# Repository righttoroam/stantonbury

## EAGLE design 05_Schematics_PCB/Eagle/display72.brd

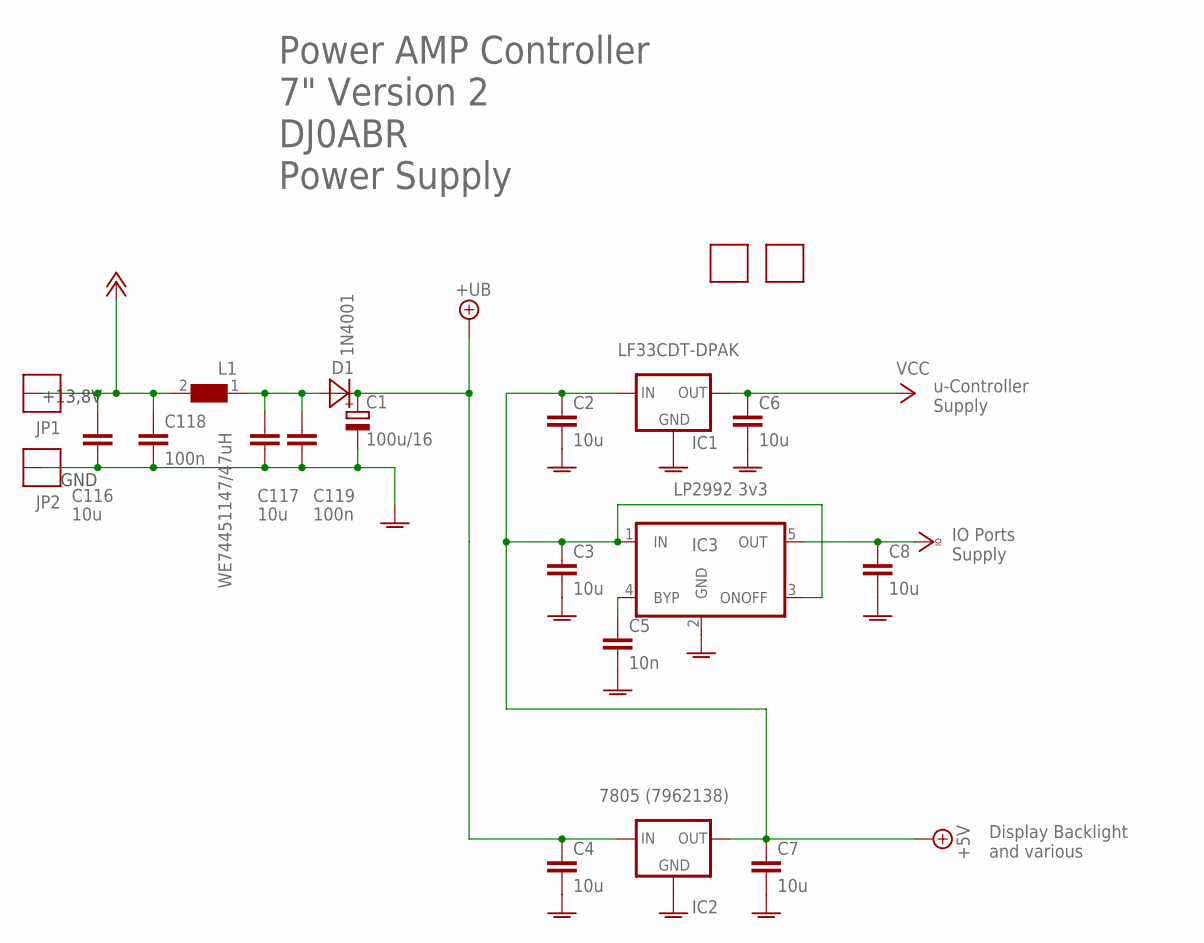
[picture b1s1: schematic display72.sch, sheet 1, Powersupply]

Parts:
C1: 100u/16; E2,5-7
C2, C3, C4, C116, C117: 10u; C0805
C5: 10n; C0603
C6, C7, C8: 10u; C0603
C118, C119: 100n; C0603
D1: 1N4001; MELF
FID1, FID2: FIDUCIAL
IC1: LF33CDT-DPAK; DPACK
IC2: 7805 (7962138); 78SR_SWITCHREG
IC3: LP2992 3v3; SOT23-5
JP1, JP2: THICKPINSQUARE; THICKPIN
L1: WE74451147/47uH; S

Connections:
+5V: C2.1, C3.1, C7.1, IC1.1 (IN), IC2.3 (OUT), IC3.1 (IN), IC3.3 (ONOFF); also elsewhere on the board
+UB: C1.+, C4.1, D1.1 (C), IC2.1 (IN)
AGND: C1.-, C2.2, C3.2, C4.2, C5.2, C6.2, C7.2, C8.2, C116.2, C117.2, C118.2, C119.2, IC1.4 (GND), IC2.2 (GND), IC3.2 (GND), JP2.1; also elsewhere on the board
unnamed: C117.1, C119.1, D1.2 (A), L1.1
unnamed: C5.1, IC3.4 (BYP)
PLUSZWOELF: C116.1, C118.1, JP1.1, L1.2; also elsewhere on the board
VCC: C6.1, IC1.3 (OUT); also elsewhere on the board
VCCIO: C8.1, IC3.5 (OUT); also elsewhere on the board

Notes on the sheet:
GND
+13,8V
Power AMP Controller 7" Version 2 DJ0ABR Power Supply
u-Controller Supply
IO Ports Supply
Display Backlight and various

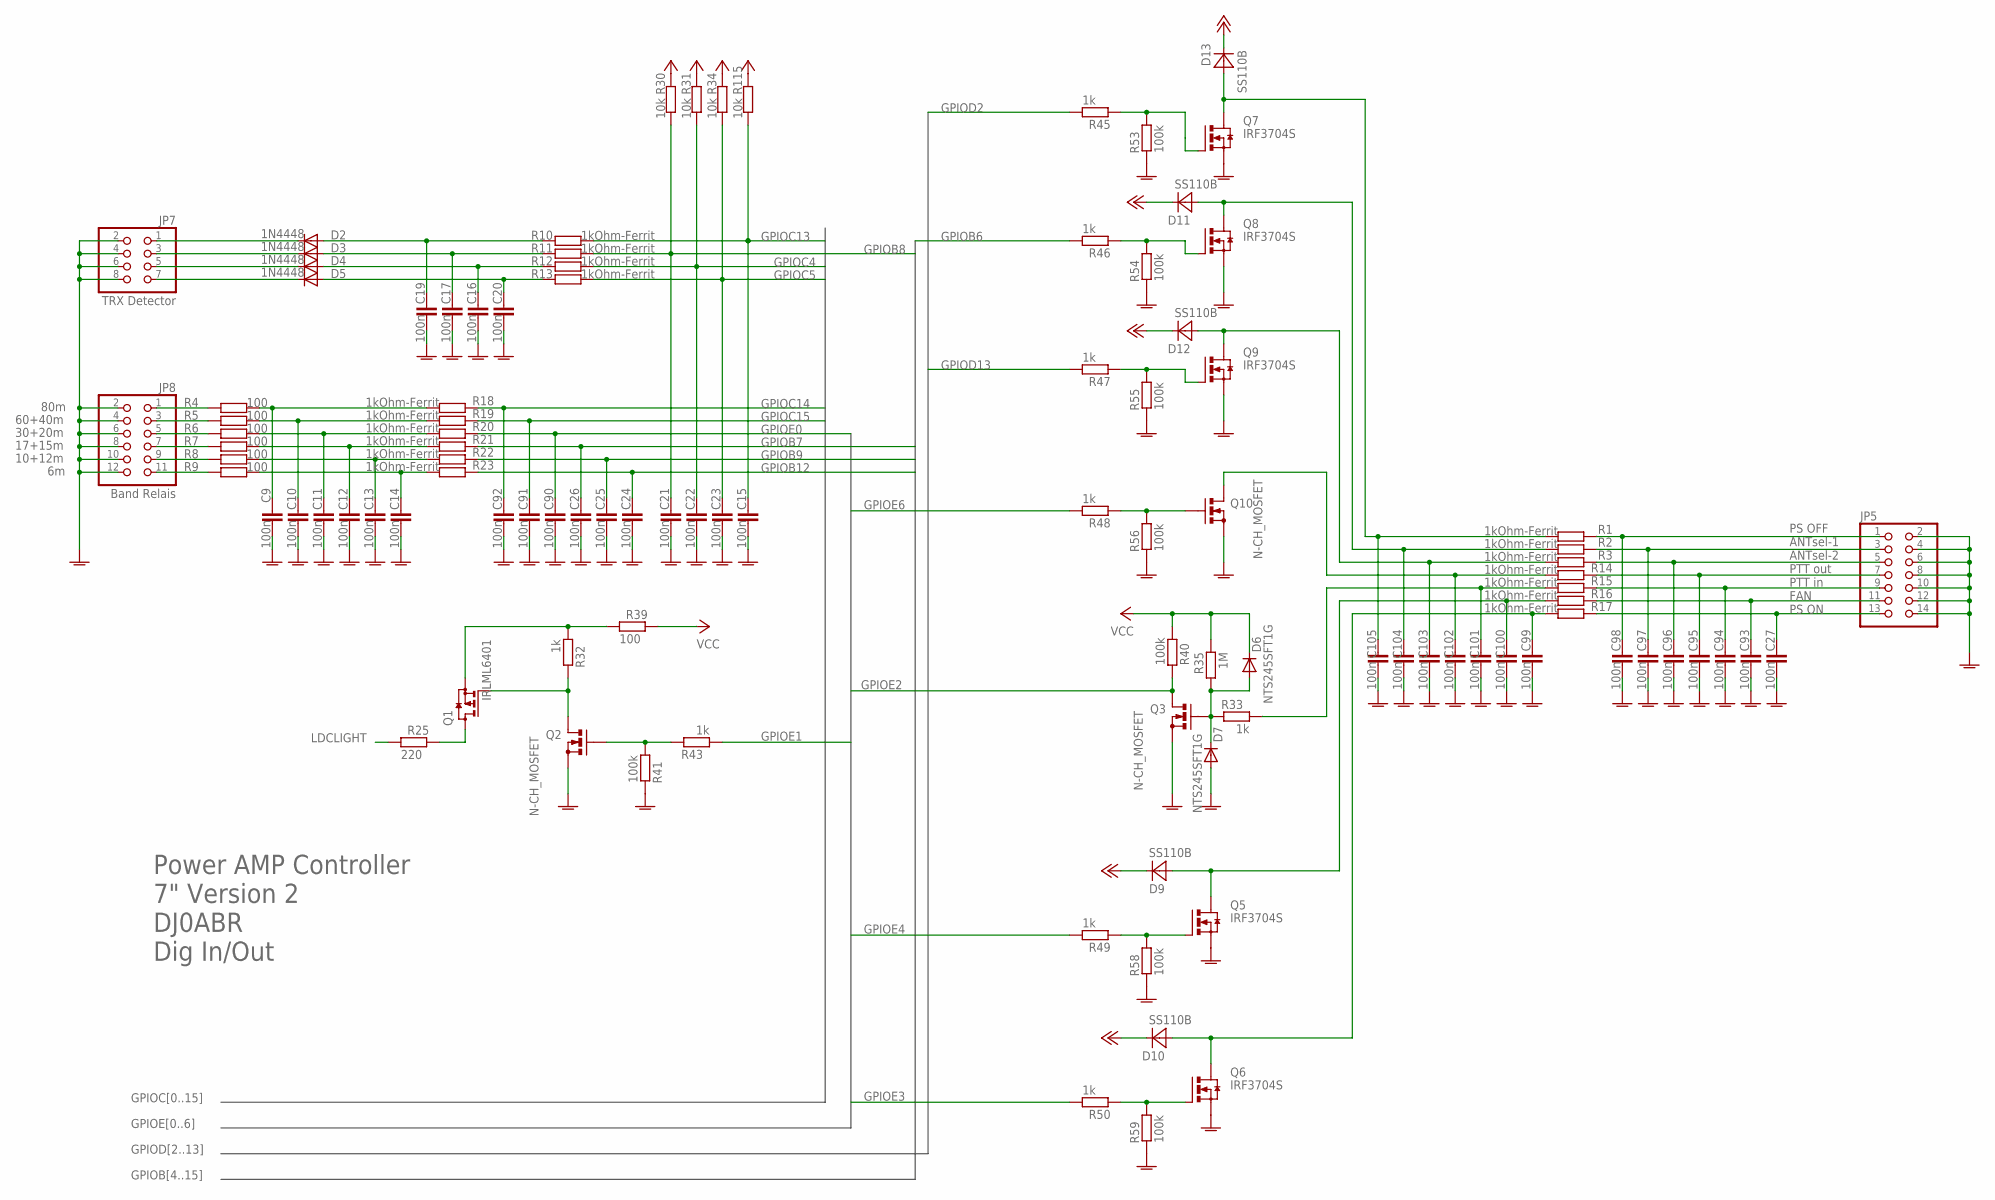
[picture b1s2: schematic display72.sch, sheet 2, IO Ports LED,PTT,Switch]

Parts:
C9, C10, C11, C12, C13, C14, C15, C16, C17, C19, C20, C21, C22, C23, C24, C25, C26, C27, C90, C91, C92, C93, C94, C95, C96, C97, C98, C99, C100, C101, C102, C103, C104, C105: 100n; C0603
D2, D3, D4, D5: 1N4448; SOD523
D6, D7: NTS245SFT1G; MINIMELF
D9, D10, D11, D12, D13: SS110B; MELF
JP5: PINHD-2X7/90; 2X07/90
JP7: TRX Detector; 2X04/90
JP8: Band Relais; 2X06/90
Q1: IRLML6401; SOT23
Q2, Q3, Q10: N-CH_MOSFET; SOT23
Q5, Q6, Q7, Q8, Q9: IRF3704S; D2PACK
R1, R2, R3, R10, R11, R12, R13, R14, R15, R16, R17, R18, R19, R20, R21, R22, R23: 1kOhm-Ferrit; R0603
R4, R5, R6, R7, R8, R9, R39: 100; R0603
R25: 220; R0603
R30, R31, R34, R115: 10k; R0603
R32, R33, R43, R45, R46, R47, R48, R49, R50: 1k; R0603
R35: 1M; R0603
R40, R41, R53, R54, R55, R56, R58, R59: 100k; R0603

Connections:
AGND: C9.2, C10.2, C11.2, C12.2, C13.2, C14.2, C15.2, C16.2, C17.2, C19.2, C20.2, C21.2, C22.2, C23.2, C24.2, C25.2, C26.2, C27.2, C90.2, C91.2, C92.2, C93.2, C94.2, C95.2, C96.2, C97.2, C98.2, C99.2, C100.2, C101.2, C102.2, C103.2, C104.2, C105.2, D7.A, JP5.2, JP5.4, JP5.6, JP5.8, JP5.10, JP5.12, JP5.14, JP7.2, JP7.4, JP7.6, JP7.8, JP8.2, JP8.4, JP8.6, JP8.8, JP8.10, JP8.12, Q2.2 (S), Q3.2 (S), Q5.3 (S), Q6.3 (S), Q7.3 (S), Q8.3 (S), Q9.3 (S), Q10.2 (S), R41.2, R53.2, R54.2, R55.2, R56.2, R58.2, R59.2; also elsewhere on the board
GPIOB6: R46.1; also elsewhere on the board
GPIOB7: C26.1, R21.1; also elsewhere on the board
GPIOB8: C21.1, R11.2, R30.1; also elsewhere on the board
GPIOB9: C25.1, R22.1; also elsewhere on the board
GPIOB12: C24.1, R23.1; also elsewhere on the board
GPIOC4: C22.1, R12.2, R31.1; also elsewhere on the board
GPIOC5: C23.1, R13.2, R34.1; also elsewhere on the board
GPIOC13: C15.1, R10.2, R115.1; also elsewhere on the board
GPIOC14: C92.1, R18.1; also elsewhere on the board
GPIOC15: C91.1, R19.1; also elsewhere on the board
GPIOD2: R45.1; also elsewhere on the board
GPIOD13: R47.1; also elsewhere on the board
GPIOE0: C90.1, R20.1; also elsewhere on the board
GPIOE1: R43.1; also elsewhere on the board
GPIOE2: Q3.3 (D), R40.1; also elsewhere on the board
GPIOE3: R50.1; also elsewhere on the board
GPIOE4: R49.1; also elsewhere on the board
GPIOE6: R48.1; also elsewhere on the board
LDCLIGHT: R25.1; also elsewhere on the board
unnamed: Q10.1 (G), R48.2, R56.1
unnamed: C102.1, Q10.3 (D), R14.2
unnamed: D6.A, D7.C, Q3.1 (G), R33.2, R35.2
unnamed: Q2.1 (G), R41.1, R43.2
unnamed: Q1.1 (G), Q2.3 (D), R32.2
unnamed: Q1.3 (D), R25.2
unnamed: JP8.1, R4.1
unnamed: C98.1, JP5.1, R1.1
unnamed: Q9.1 (G), R47.2, R55.1
unnamed: C103.1, D12.2 (A), Q9.2 (D), R3.2
unnamed: C97.1, JP5.3, R2.1
unnamed: C96.1, JP5.5, R3.1
unnamed: C95.1, JP5.7, R14.1
unnamed: C94.1, JP5.9, R15.1
unnamed: C93.1, JP5.11, R16.1
unnamed: D3.C, JP7.3
unnamed: D4.C, JP7.5
unnamed: D5.C, JP7.7
unnamed: C27.1, JP5.13, R17.1
unnamed: C9.1, R4.2, R18.2
unnamed: C14.1, R9.2, R23.2
unnamed: C13.1, R8.2, R22.2
unnamed: C12.1, R7.2, R21.2
unnamed: C11.1, R6.2, R20.2
unnamed: C10.1, R5.2, R19.2
unnamed: Q1.2 (S), R32.1, R39.1
unnamed: D2.C, JP7.1
unnamed: Q8.1 (G), R46.2, R54.1
unnamed: C104.1, D11.2 (A), Q8.2 (D), R2.2
unnamed: JP8.3, R5.1
unnamed: JP8.5, R6.1
unnamed: Q7.1 (G), R45.2, R53.1
unnamed: JP8.7, R7.1
unnamed: JP8.9, R8.1
unnamed: JP8.11, R9.1
unnamed: C105.1, D13.2 (A), Q7.2 (D), R1.2
unnamed: C19.1, D2.A, R10.1
unnamed: C17.1, D3.A, R11.1
unnamed: C16.1, D4.A, R12.1
unnamed: C20.1, D5.A, R13.1
unnamed: C100.1, D9.2 (A), Q5.2 (D), R16.2
unnamed: Q5.1 (G), R49.2, R58.1
unnamed: C99.1, D10.2 (A), Q6.2 (D), R17.2
unnamed: Q6.1 (G), R50.2, R59.1
PLUSZWOELF: D9.1 (C), D10.1 (C), D11.1 (C), D12.1 (C), D13.1 (C); also elsewhere on the board
PTT: C101.1, R15.2, R33.1
VCC: D6.C, R30.2, R31.2, R34.2, R35.1, R39.2, R40.2, R115.2; also elsewhere on the board

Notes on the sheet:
80m
60+40m
30+20m
17+15m
10+12m
Power AMP Controller 7" Version 2 DJ0ABR Dig In/Out
PS OFF ANTsel-1 ANTsel-2 PTT out PTT in FAN PS ON

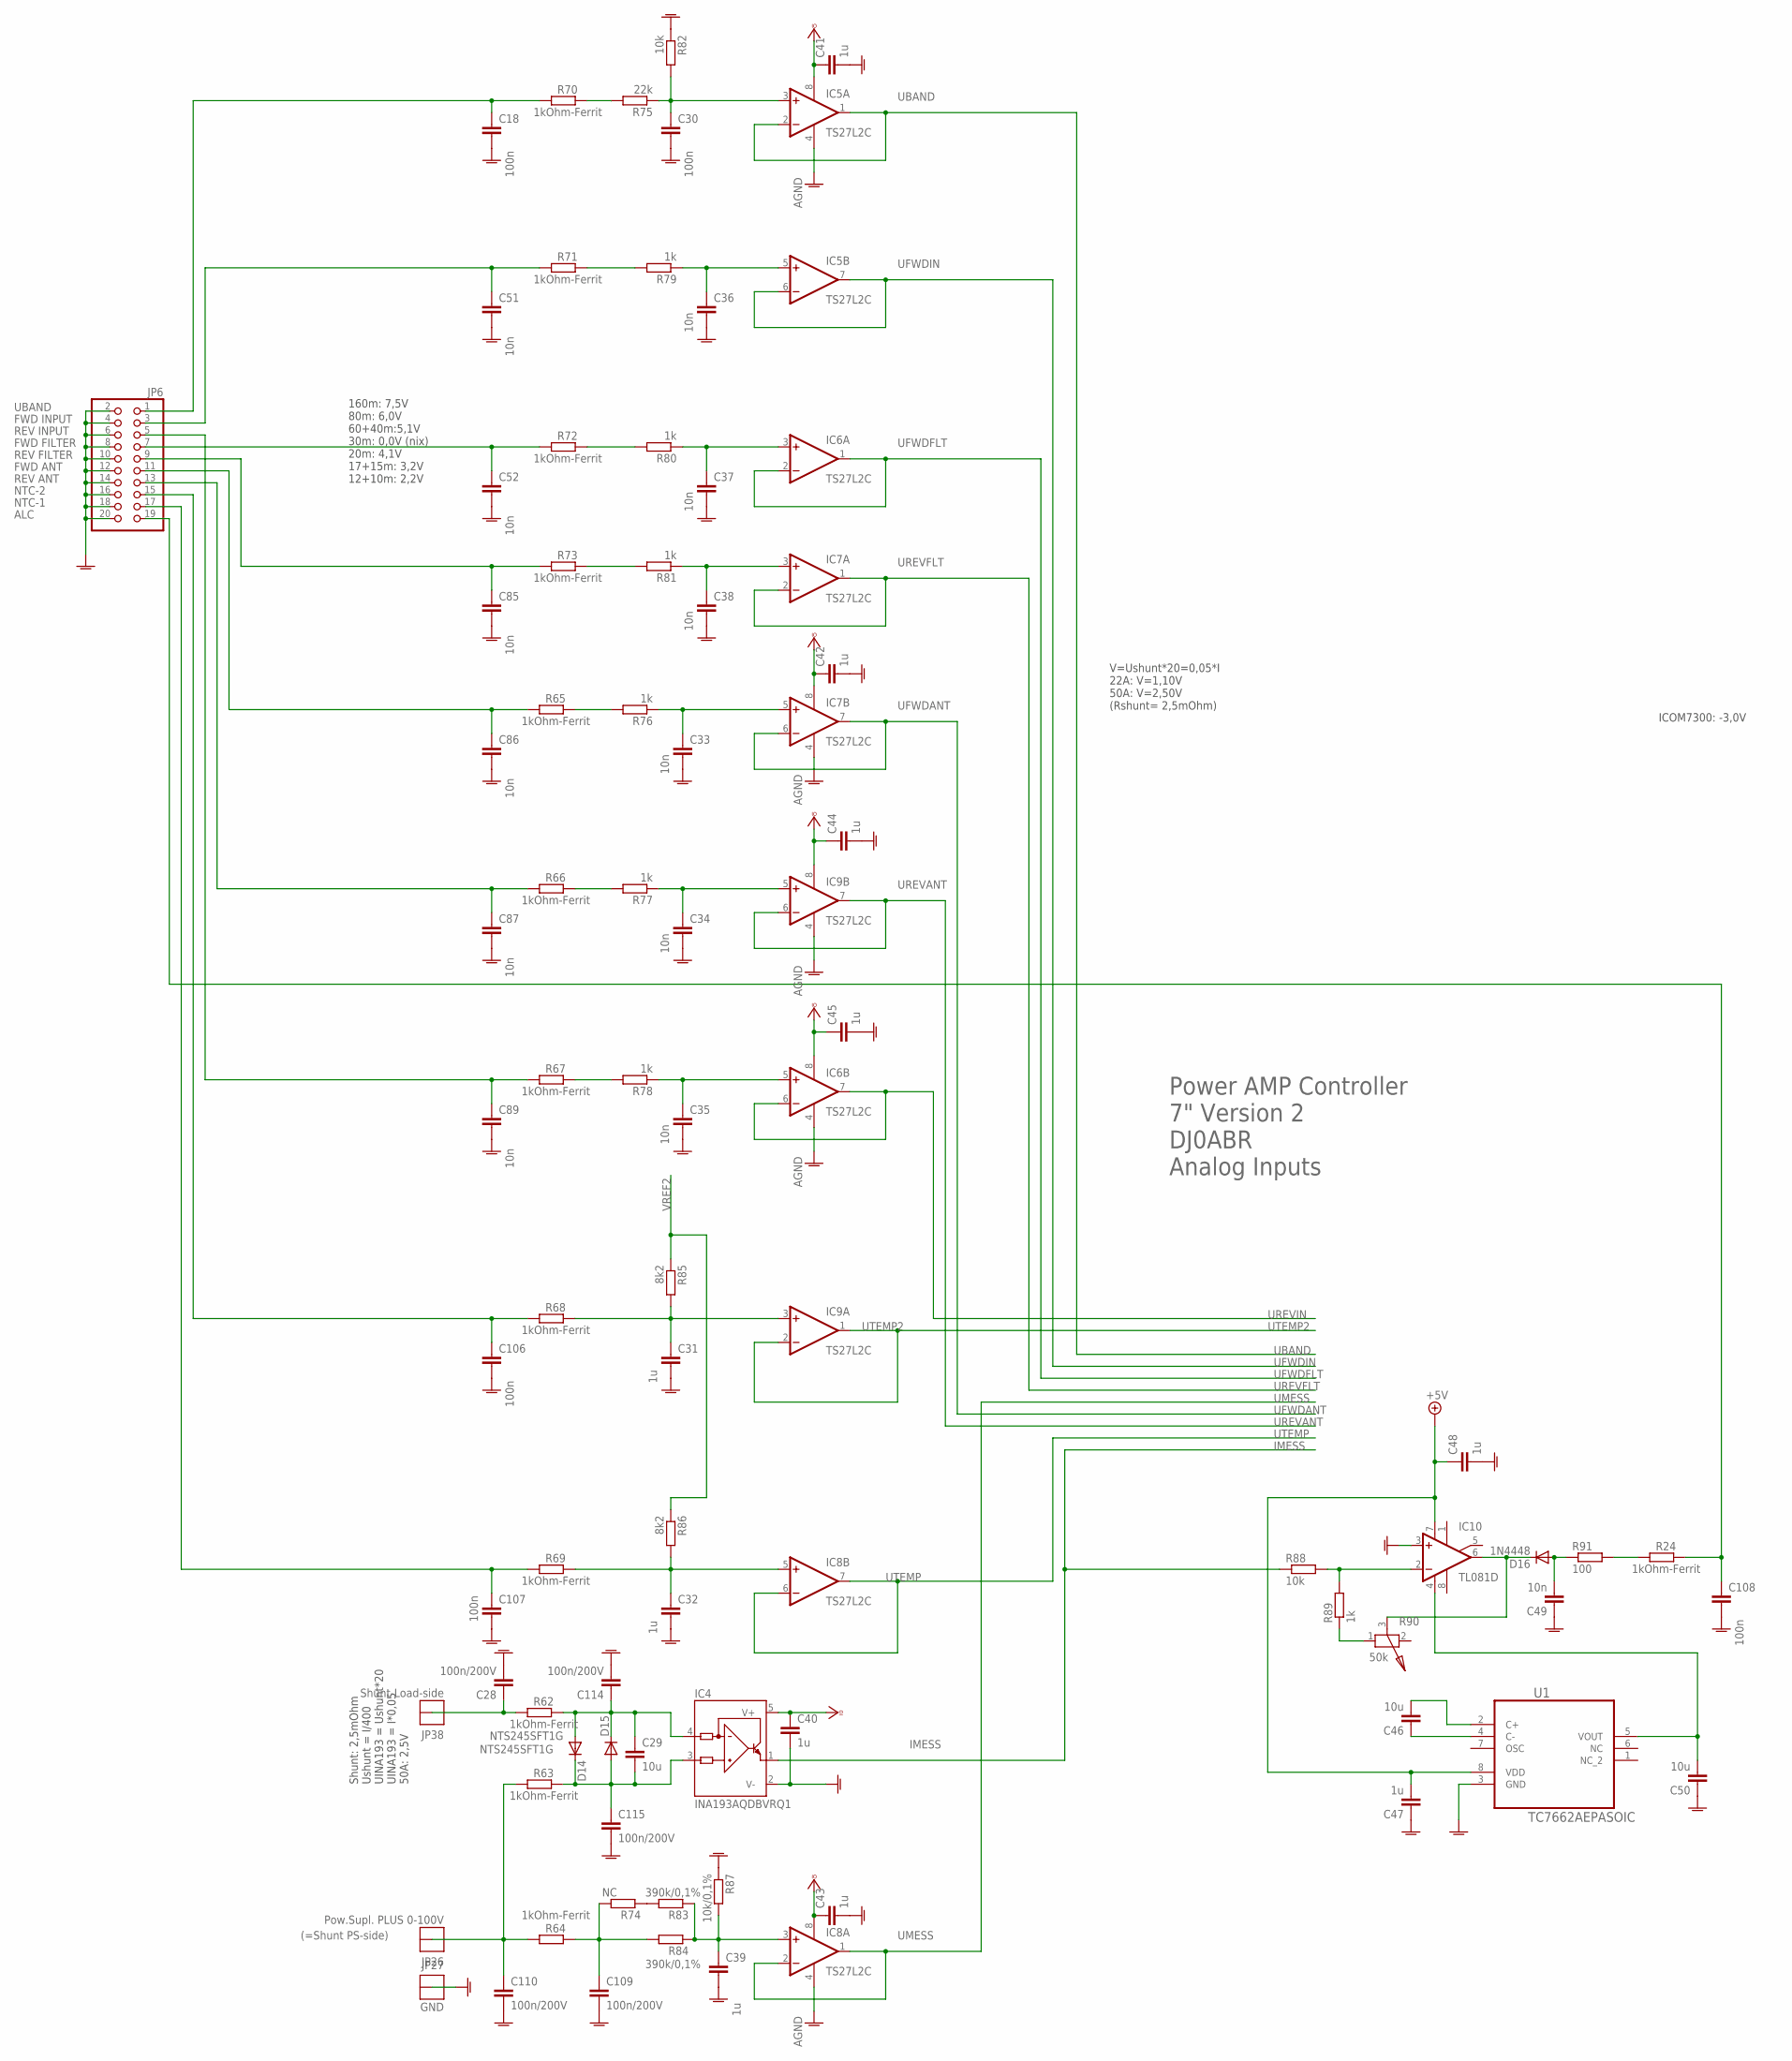
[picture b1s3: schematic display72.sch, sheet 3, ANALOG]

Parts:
C18, C30, C106, C107, C108: 100n; C0603
C28, C109, C110, C114, C115: 100n/200V; C1206K
C29: 10u; C0805
C31, C32, C39, C40, C41, C42, C43, C44, C45, C47, C48: 1u; C0603
C33, C34, C35, C36, C37, C38, C49, C51, C52, C85, C86, C87, C89: 10n; C0603
C46, C50: 10u; C0603
D14, D15: NTS245SFT1G; MINIMELF
D16: 1N4448; SOD523
IC4: INA193AQDBVRQ1; SOT23-5
IC5, IC6, IC7, IC8, IC9: TS27L2C; SO08
IC10: TL081D; SO08
JP6: PINHD-2X10/90; 2X10/90
JP26: Pow.Supl. PLUS 0-100V; THICKPIN
JP27: GND; THICKPIN
JP38: Shunt-Load-side; THICKPIN
R24, R62, R63, R64, R65, R66, R67, R68, R69, R70, R71, R72, R73: 1kOhm-Ferrit; R0603
R74: NC; R0603
R75: 22k; R0603
R76, R77, R78, R79, R80, R81, R89: 1k; R0603
R82, R88: 10k; R0603
R83, R84: 390k/0,1%; R0603
R85, R86: 8k2; R0603
R87: 10k/0,1%; R0603
R90: 50k; MINIPOTI
R91: 100; R0603
U1: TC7662AEPASOIC; SO-8

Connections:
+5V: C47.2, C48.1, IC10.7 (V+), U1.8 (VDD); also elsewhere on the board
AGND: C18.2, C28.2, C30.2, C31.2, C32.2, C33.2, C34.2, C35.2, C36.2, C37.2, C38.2, C39.2, C40.2, C41.2, C42.2, C43.2, C44.2, C45.2, C47.1, C48.2, C49.1, C50.1, C51.2, C52.2, C85.2, C86.2, C87.2, C89.2, C106.2, C107.2, C108.2, C109.2, C110.2, C114.2, C115.2, IC4.2 (V-), IC5.4 (V-), IC6.4 (V-), IC7.4 (V-), IC8.4 (V-), IC9.4 (V-), IC10.3 (+IN), JP6.2, JP6.4, JP6.6, JP6.8, JP6.10, JP6.12, JP6.14, JP6.16, JP6.18, JP6.20, JP27.1, R82.1, R87.1, U1.3 (GND); also elsewhere on the board
IMESS: IC4.1 (OUT), R88.1; also elsewhere on the board
unnamed: R24.1, R91.2
unnamed: R70.2, R75.2
unnamed: R71.2, R79.2
unnamed: R72.2, R80.2
unnamed: C30.1, IC5.3 (+IN), R75.1, R82.2
unnamed: C18.1, JP6.1, R70.1
unnamed: R73.2, R81.2
unnamed: C109.1, R64.2, R74.2, R84.2
unnamed: R65.2, R76.2
unnamed: R66.2, R77.2
unnamed: C39.1, IC8.3 (+IN), R83.1, R84.1, R87.2
unnamed: C33.1, IC7.5 (+IN), R76.1
unnamed: C86.1, JP6.11, R65.1
unnamed: C34.1, IC9.5 (+IN), R77.1
unnamed: C87.1, JP6.13, R66.1
unnamed: C29.1, C114.1, D14.A, D15.C, IC4.4 (IN-), R62.2
unnamed: C29.2, C115.1, D14.C, D15.A, IC4.3 (IN+), R63.2
unnamed: C28.1, JP38.1, R62.1
unnamed: C110.1, JP26.1, R63.1, R64.1
unnamed: C32.1, IC8.5 (+IN), R69.2, R86.2
unnamed: C107.1, JP6.17, R69.1
unnamed: C38.1, IC7.3 (+IN), R81.1
unnamed: C85.1, JP6.9, R73.1
unnamed: C37.1, IC6.3 (+IN), R80.1
unnamed: C52.1, JP6.7, R72.1
unnamed: C36.1, IC5.5 (+IN), R79.1
unnamed: C51.1, JP6.3, R71.1
unnamed: C35.1, IC6.5 (+IN), R78.1
unnamed: C89.1, JP6.5, R67.1
unnamed: R67.2, R78.2
unnamed: C31.1, IC9.3 (+IN), R68.2, R85.2
unnamed: C106.1, JP6.15, R68.1
unnamed: R74.1, R83.2
unnamed: C46.1, U1.4 (C-)
unnamed: C46.2, U1.2 (C+)
unnamed: C50.2, IC10.4 (V-), U1.5 (VOUT)
unnamed: D16.C, IC10.6 (OUT), R90.3
unnamed: C108.1, JP6.19, R24.2
unnamed: IC10.2 (-IN), R88.2, R89.2
unnamed: R89.1, R90.1
unnamed: C49.2, D16.A, R91.1
UBAND: IC5.1 (OUT), IC5.2 (-IN); also elsewhere on the board
UFWDANT: IC7.6 (-IN), IC7.7 (OUT); also elsewhere on the board
UFWDFLT: IC6.1 (OUT), IC6.2 (-IN); also elsewhere on the board
UFWDIN: IC5.6 (-IN), IC5.7 (OUT); also elsewhere on the board
UMESS: IC8.1 (OUT), IC8.2 (-IN); also elsewhere on the board
UREVANT: IC9.6 (-IN), IC9.7 (OUT); also elsewhere on the board
UREVFLT: IC7.1 (OUT), IC7.2 (-IN); also elsewhere on the board
UREVIN: IC6.6 (-IN), IC6.7 (OUT); also elsewhere on the board
UTEMP: IC8.6 (-IN), IC8.7 (OUT); also elsewhere on the board
UTEMP2: IC9.1 (OUT), IC9.2 (-IN); also elsewhere on the board
VCCIO: C40.1, C41.1, C42.1, C43.1, C44.1, C45.1, IC4.5 (V+), IC5.8 (V+), IC6.8 (V+), IC7.8 (V+), IC8.8 (V+), IC9.8 (V+); also elsewhere on the board
VREF2: R85.1, R86.1; also elsewhere on the board

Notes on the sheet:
V=Ushunt*20=0,05*I 22A: V=1,10V 50A: V=2,50V (Rshunt= 2,5mOhm)
ICOM7300: -3,0V
160m: 7,5V 80m: 6,0V 60+40m:5,1V 30m: 0,0V (nix) 20m: 4,1V 17+15m: 3,2V 12+10m: 2,2V
Shunt: 2,5mOhm Ushunt = I/400 UINA193 = Ushunt*20 UINA193 = I*0,05 50A: 2,5V
Power AMP Controller 7" Version 2 DJ0ABR Analog Inputs
UBAND
FWD INPUT
REV INPUT
FWD FILTER
REV FILTER
FWD ANT
REV ANT
NTC-2
NTC-1
ALC
(=Shunt PS-side)

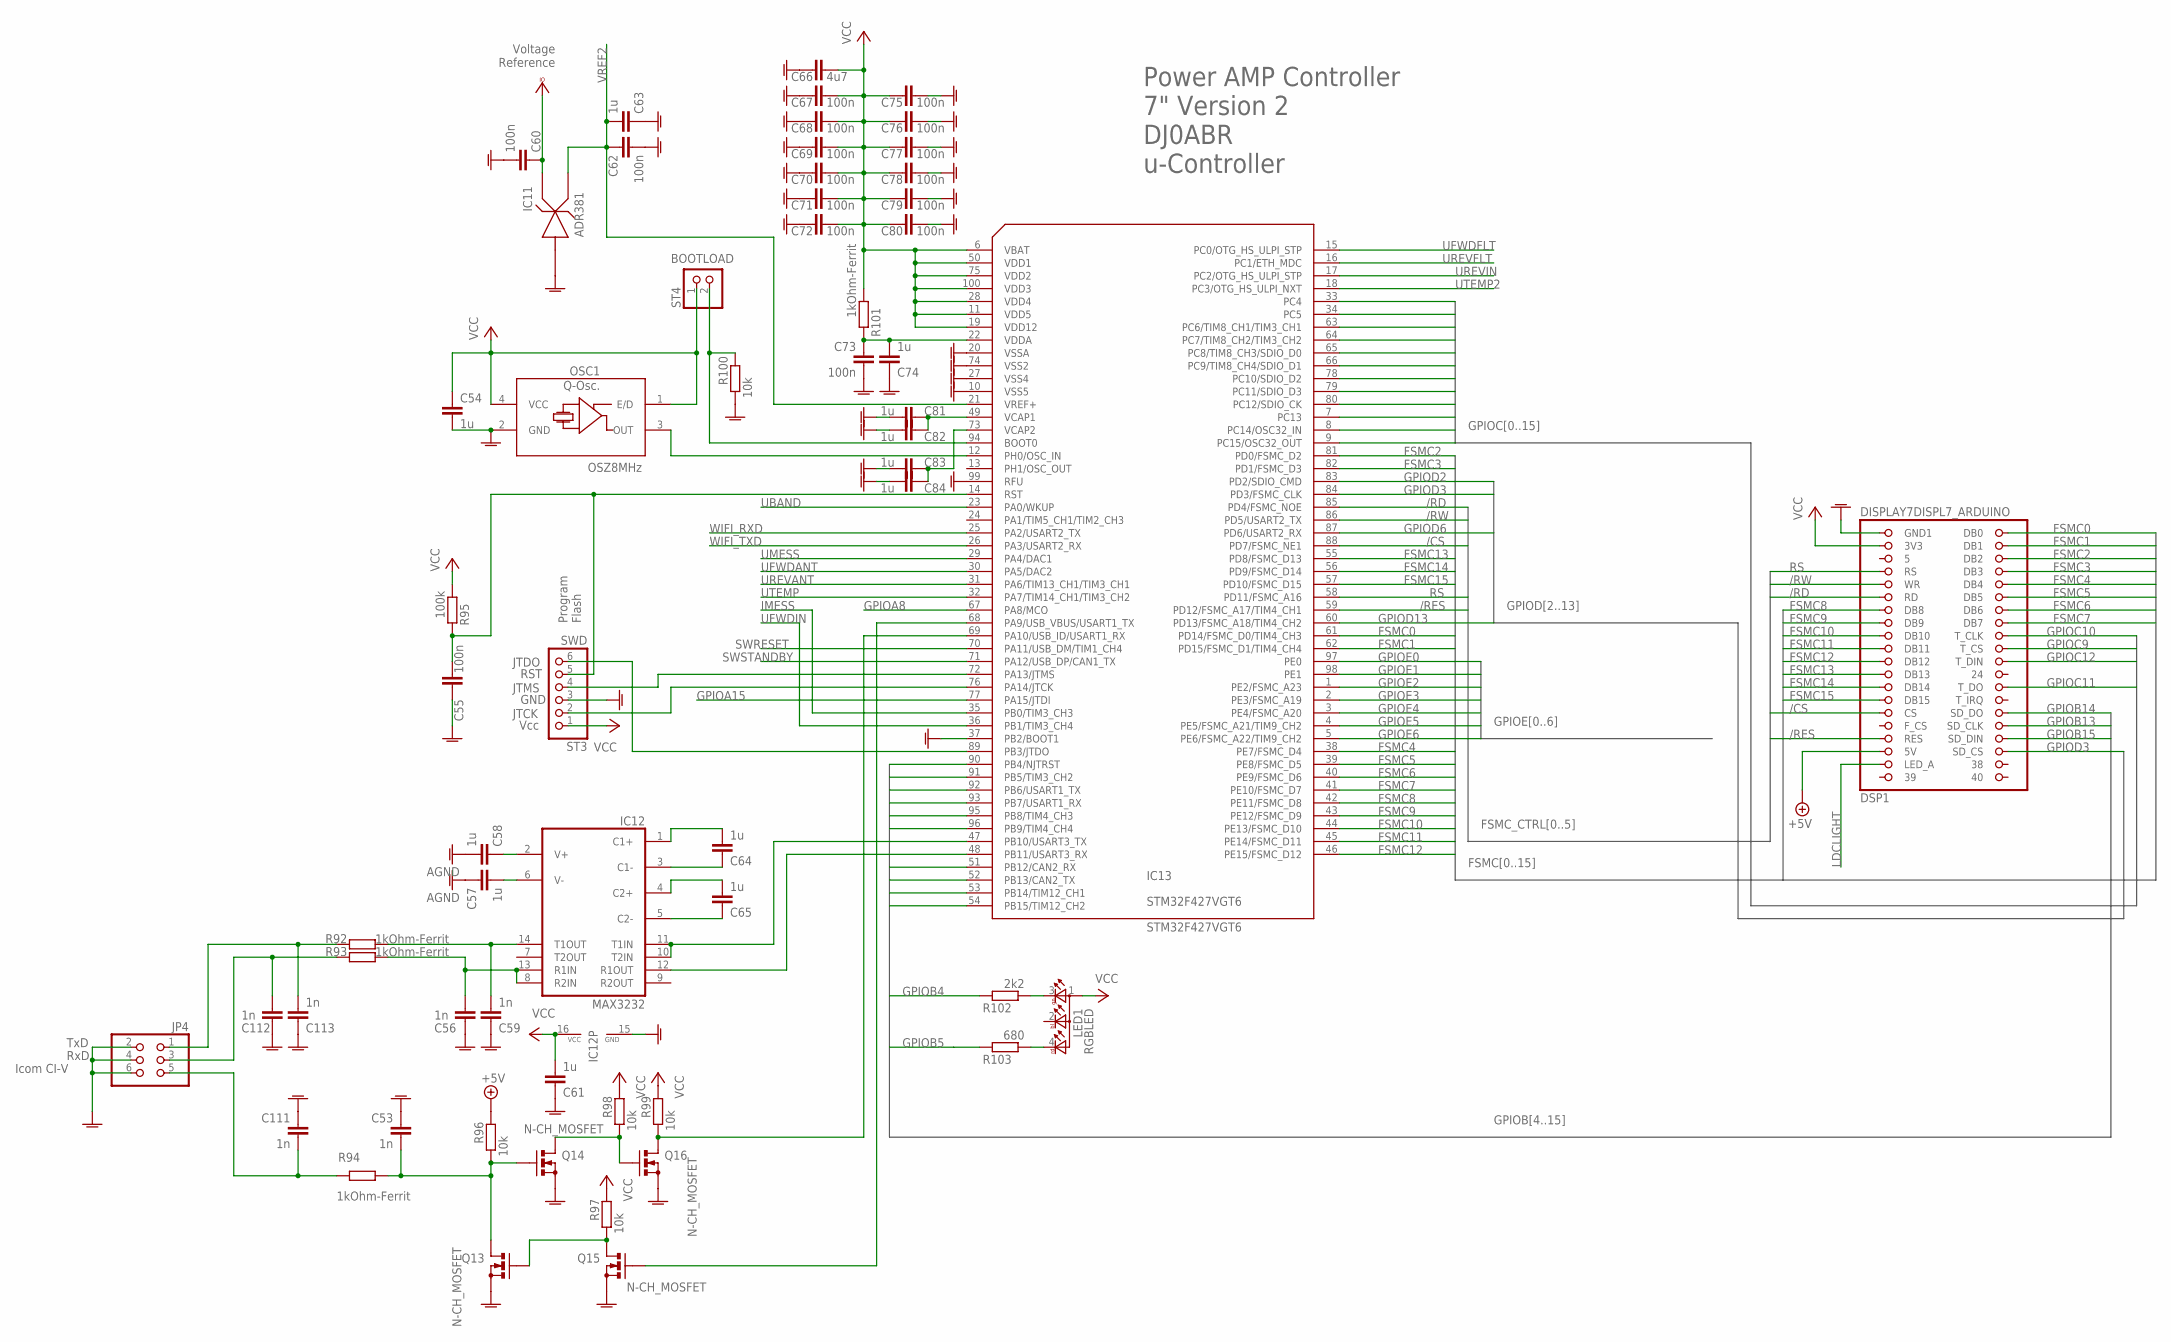
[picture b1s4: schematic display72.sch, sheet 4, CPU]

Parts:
C53, C56, C59, C111, C112, C113: 1n; C0603
C54, C57, C58, C64, C65, C81, C82, C83, C84: 1u; C0603K
C55, C60, C62, C67, C68, C69, C70, C71, C72, C73, C75, C76, C77, C78, C79, C80: 100n; C0603
C61, C63, C74: 1u; C0603
C66: 4u7; C0603
DSP1: DISPLAY7DISPL7_ARDUINO; 2X20
IC11: ADR381; SOT23
IC12: MAX3232; SO16
IC13: STM32F427VGT6; TQFP100
JP4: PINHD-2X3/90; 2X03/90
LED1: RGBLED; PLCC4_WE_LED
OSC1: OSZ8MHz; QOSC_AQO7015
Q13, Q14, Q15, Q16: N-CH_MOSFET; SOT23
R92, R93, R94, R101: 1kOhm-Ferrit; R0603
R95: 100k; R0603
R96, R97, R98, R99, R100: 10k; R0603
R102: 2k2; R0603
R103: 680; R0603
ST3: SWD; PINHEAD6X1
ST4: PINHEAD2X1SMALL; PINHEAD1X2

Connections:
+5V: DSP1.35 (5V), R96.2; also elsewhere on the board
/CS: DSP1.29 (CS), IC13.88 (PD7/FSMC_NE1)
/RD: DSP1.11 (RD), IC13.85 (PD4/FSMC_NOE)
/RES: DSP1.33 (RES), IC13.59 (PD12/FSMC_A17/TIM4_CH1)
/RW: DSP1.9 (WR), IC13.86 (PD5/USART2_TX)
AGND: C53.1, C54.2, C55.1, C56.1, C57.1, C58.2, C59.1, C60.2, C61.1, C62.2, C63.1, C66.1, C67.1, C68.1, C69.1, C70.1, C71.1, C72.1, C73.2, C74.1, C75.2, C76.2, C77.2, C78.2, C79.2, C80.2, C81.1, C82.1, C83.1, C84.1, C111.1, C112.1, C113.1, DSP1.1 (GND1), IC11.3 (A), IC12.15 (GND), IC13.10 (VSS5), IC13.20 (VSSA), IC13.27 (VSS4), IC13.37 (PB2/BOOT1), IC13.74 (VSS2), IC13.99 (RFU), JP4.2, JP4.4, JP4.6, OSC1.2 (GND), Q13.2 (S), Q14.2 (S), Q15.2 (S), Q16.2 (S), R100.1, ST3.3; also elsewhere on the board
FSMC0: DSP1.2 (DB0), IC13.61 (PD14/FSMC_D0/TIM4_CH3)
FSMC1: DSP1.4 (DB1), IC13.62 (PD15/FSMC_D1/TIM4_CH4)
FSMC2: DSP1.6 (DB2), IC13.81 (PD0/FSMC_D2)
FSMC3: DSP1.8 (DB3), IC13.82 (PD1/FSMC_D3)
FSMC4: DSP1.10 (DB4), IC13.38 (PE7/FSMC_D4)
FSMC5: DSP1.12 (DB5), IC13.39 (PE8/FSMC_D5)
FSMC6: DSP1.14 (DB6), IC13.40 (PE9/FSMC_D6)
FSMC7: DSP1.16 (DB7), IC13.41 (PE10/FSMC_D7)
FSMC8: DSP1.13 (DB8), IC13.42 (PE11/FSMC_D8)
FSMC9: DSP1.15 (DB9), IC13.43 (PE12/FSMC_D9)
FSMC10: DSP1.17 (DB10), IC13.44 (PE13/FSMC_D10)
FSMC11: DSP1.19 (DB11), IC13.45 (PE14/FSMC_D11)
FSMC12: DSP1.21 (DB12), IC13.46 (PE15/FSMC_D12)
FSMC13: DSP1.23 (DB13), IC13.55 (PD8/FSMC_D13)
FSMC14: DSP1.25 (DB14), IC13.56 (PD9/FSMC_D14)
FSMC15: DSP1.27 (DB15), IC13.57 (PD10/FSMC_D15)
GPIOA8: IC13.67 (PA8/MCO)
GPIOA15: IC13.77 (PA15/JTDI)
GPIOB4: IC13.90 (PB4/NJTRST), R102.2
GPIOB5: IC13.91 (PB5/TIM3_CH2), R103.2
GPIOB6: IC13.92 (PB6/USART1_TX); also elsewhere on the board
GPIOB7: IC13.93 (PB7/USART1_RX); also elsewhere on the board
GPIOB8: IC13.95 (PB8/TIM4_CH3); also elsewhere on the board
GPIOB9: IC13.96 (PB9/TIM4_CH4); also elsewhere on the board
GPIOB12: IC13.51 (PB12/CAN2_RX); also elsewhere on the board
GPIOB13: DSP1.32 (SD_CLK), IC13.52 (PB13/CAN2_TX)
GPIOB14: DSP1.30 (SD_DO), IC13.53 (PB14/TIM12_CH1)
GPIOB15: DSP1.34 (SD_DIN), IC13.54 (PB15/TIM12_CH2)
GPIOC4: IC13.33 (PC4); also elsewhere on the board
GPIOC5: IC13.34 (PC5); also elsewhere on the board
GPIOC6: IC13.63 (PC6/TIM8_CH1/TIM3_CH1)
GPIOC7: IC13.64 (PC7/TIM8_CH2/TIM3_CH2)
GPIOC8: IC13.65 (PC8/TIM8_CH3/SDIO_D0)
GPIOC9: DSP1.20 (T_CS), IC13.66 (PC9/TIM8_CH4/SDIO_D1)
GPIOC10: DSP1.18 (T_CLK), IC13.78 (PC10/SDIO_D2)
GPIOC11: DSP1.26 (T_DO), IC13.79 (PC11/SDIO_D3)
GPIOC12: DSP1.22 (T_DIN), IC13.80 (PC12/SDIO_CK)
GPIOC13: IC13.7 (PC13); also elsewhere on the board
GPIOC14: IC13.8 (PC14/OSC32_IN); also elsewhere on the board
GPIOC15: IC13.9 (PC15/OSC32_OUT); also elsewhere on the board
GPIOD2: IC13.83 (PD2/SDIO_CMD); also elsewhere on the board
GPIOD3: DSP1.36 (SD_CS), IC13.84 (PD3/FSMC_CLK)
GPIOD6: IC13.87 (PD6/USART2_RX)
GPIOD13: IC13.60 (PD13/FSMC_A18/TIM4_CH2); also elsewhere on the board
GPIOE0: IC13.97 (PE0); also elsewhere on the board
GPIOE1: IC13.98 (PE1); also elsewhere on the board
GPIOE2: IC13.1 (PE2/FSMC_A23); also elsewhere on the board
GPIOE3: IC13.2 (PE3/FSMC_A19); also elsewhere on the board
GPIOE4: IC13.3 (PE4/FSMC_A20); also elsewhere on the board
GPIOE5: IC13.4 (PE5/FSMC_A21/TIM9_CH2)
GPIOE6: IC13.5 (PE6/FSMC_A22/TIM9_CH2); also elsewhere on the board
IMESS: IC13.35 (PB0/TIM3_CH3); also elsewhere on the board
LDCLIGHT: DSP1.37 (LED_A); also elsewhere on the board
unnamed: LED1.3 (CRED), R102.1
unnamed: C64.1, IC12.3 (C1-)
unnamed: C64.2, IC12.1 (C1+)
unnamed: C65.2, IC12.4 (C2+)
unnamed: C65.1, IC12.5 (C2-)
unnamed: C58.1, IC12.2 (V+)
unnamed: C57.2, IC12.6 (V-)
unnamed: IC12.10 (T2IN), IC12.11 (T1IN), IC13.47 (PB10/USART3_TX)
unnamed: C59.2, IC12.14 (T1OUT), R92.2
unnamed: C53.2, Q13.3 (D), Q14.1 (G), R94.2, R96.1
unnamed: IC12.12 (R1OUT), IC13.48 (PB11/USART3_RX)
unnamed: Q14.3 (D), Q16.1 (G), R98.1
unnamed: IC13.69 (PA10/USB_ID/USART1_RX), Q16.3 (D), R99.1
unnamed: C56.2, IC12.8 (R2IN), IC12.13 (R1IN), R93.2
unnamed: IC13.68 (PA9/USB_VBUS/USART1_TX), Q15.1 (G)
unnamed: Q13.1 (G), Q15.3 (D), R97.1
unnamed: LED1.4 (CGREEN), R103.1
unnamed: C113.2, JP4.1, R92.1
unnamed: C112.2, JP4.3, R93.1
unnamed: C111.2, JP4.5, R94.1
unnamed: C83.2, C84.2, IC13.73 (VCAP2)
unnamed: IC13.12 (PH0/OSC_IN), OSC1.3 (OUT)
unnamed: C81.2, C82.2, IC13.49 (VCAP1)
unnamed: C73.1, C74.2, IC13.22 (VDDA), R101.2
unnamed: C55.2, IC13.14 (RST), R95.2, ST3.5
unnamed: IC13.94 (BOOT0), R100.2, ST4.2
unnamed: IC13.76 (PA14/JTCK), ST3.2
unnamed: IC13.72 (PA13/JTMS), ST3.4
unnamed: IC13.89 (PB3/JTDO), ST3.6
RS: DSP1.7 (RS), IC13.58 (PD11/FSMC_A16)
SWRESET: IC13.70 (PA11/USB_DM/TIM1_CH4)
SWSTANDBY: IC13.71 (PA12/USB_DP/CAN1_TX)
UBAND: IC13.23 (PA0/WKUP); also elsewhere on the board
UFWDANT: IC13.30 (PA5/DAC2); also elsewhere on the board
UFWDFLT: IC13.15 (PC0/OTG_HS_ULPI_STP); also elsewhere on the board
UFWDIN: IC13.36 (PB1/TIM3_CH4); also elsewhere on the board
UMESS: IC13.29 (PA4/DAC1); also elsewhere on the board
UREVANT: IC13.31 (PA6/TIM13_CH1/TIM3_CH1); also elsewhere on the board
UREVFLT: IC13.16 (PC1/ETH_MDC); also elsewhere on the board
UREVIN: IC13.17 (PC2/OTG_HS_ULPI_STP); also elsewhere on the board
UTEMP: IC13.32 (PA7/TIM14_CH1/TIM3_CH2); also elsewhere on the board
UTEMP2: IC13.18 (PC3/OTG_HS_ULPI_NXT); also elsewhere on the board
VCC: C54.1, C61.2, C66.2, C67.2, C68.2, C69.2, C70.2, C71.2, C72.2, C75.1, C76.1, C77.1, C78.1, C79.1, C80.1, DSP1.3 (3V3), IC12.16 (VCC), IC13.6 (VBAT), IC13.11 (VDD5), IC13.19 (VDD12), IC13.28 (VDD4), IC13.50 (VDD1), IC13.75 (VDD2), IC13.100 (VDD3), LED1.1 (A2), OSC1.1 (E/D), OSC1.4 (VCC), R95.1, R97.2, R98.2, R99.2, R101.1, ST3.1, ST4.1; also elsewhere on the board
VCCIO: C60.1, IC11.1 (K2); also elsewhere on the board
VREF2: C62.1, C63.2, IC11.2 (K1), IC13.21 (VREF+); also elsewhere on the board
WIFI_RXD: IC13.25 (PA2/USART2_TX); also elsewhere on the board
WIFI_TXD: IC13.26 (PA3/USART2_RX); also elsewhere on the board

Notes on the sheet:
BOOTLOAD
Power AMP Controller 7" Version 2 DJ0ABR u-Controller
TxD
RxD
Icom CI-V
Program Flash
Voltage Reference
STM32F427VGT6
JTDO
RST
JTMS
GND
Vcc
JTCK

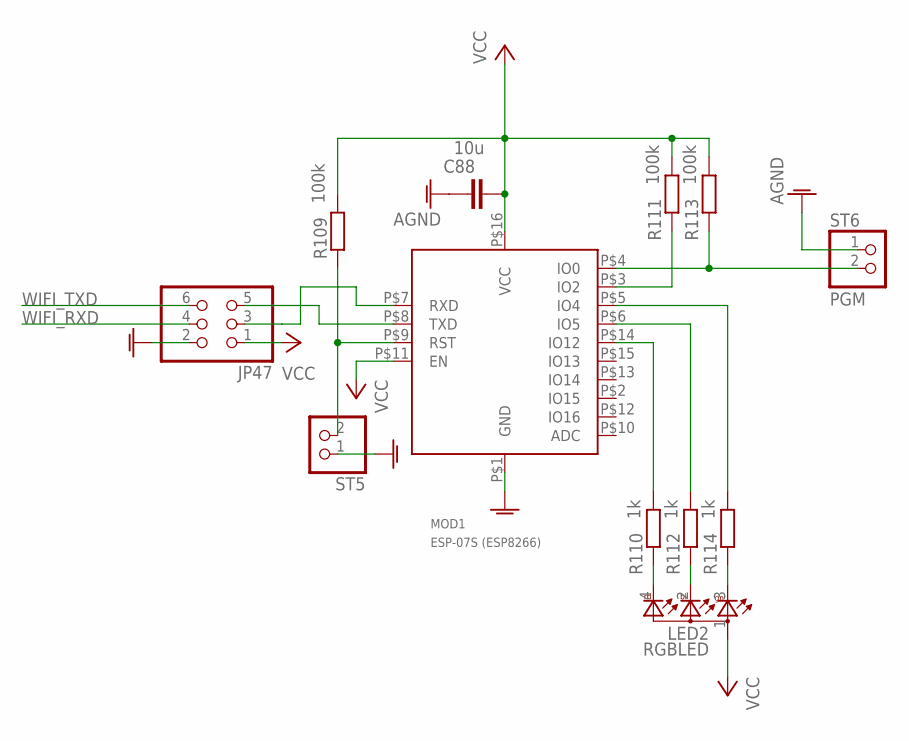
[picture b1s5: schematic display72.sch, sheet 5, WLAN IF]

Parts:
C88: 10u; C0805K
JP47: PINHD-2X3; 2X03
LED2: RGBLED; PLCC4_WE_LED
MOD1: ESP-07S (ESP8266); ESP8266-12
R109, R111, R113: 100k; R0603
R110, R112, R114: 1k; R0603
ST5: PINHEAD2X1BIG; PINHEAD1X2BIG
ST6: PGM; PINHEAD1X2

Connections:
AGND: C88.1, JP47.2, MOD1.P$1 (GND), ST5.1, ST6.1; also elsewhere on the board
unnamed: MOD1.P$4 (IO0), R113.1, ST6.2
unnamed: LED2.3 (CRED), R114.1
unnamed: LED2.2 (CBLUE), R112.1
unnamed: LED2.4 (CGREEN), R110.1
unnamed: MOD1.P$14 (IO12), R110.2
unnamed: MOD1.P$6 (IO5), R112.2
unnamed: MOD1.P$9 (RST), R109.1, ST5.2
unnamed: MOD1.P$3 (IO2), R111.1
unnamed: MOD1.P$5 (IO4), R114.2
unnamed: JP47.3, MOD1.P$7 (RXD)
unnamed: JP47.5, MOD1.P$8 (TXD)
VCC: C88.2, JP47.1, LED2.1 (A2), MOD1.P$11 (EN), MOD1.P$16 (VCC), R109.2, R111.2, R113.2; also elsewhere on the board
WIFI_RXD: JP47.4; also elsewhere on the board
WIFI_TXD: JP47.6; also elsewhere on the board
